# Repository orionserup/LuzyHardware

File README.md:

# LuzyHardware
A Hardware device that glows different colors depending on settings

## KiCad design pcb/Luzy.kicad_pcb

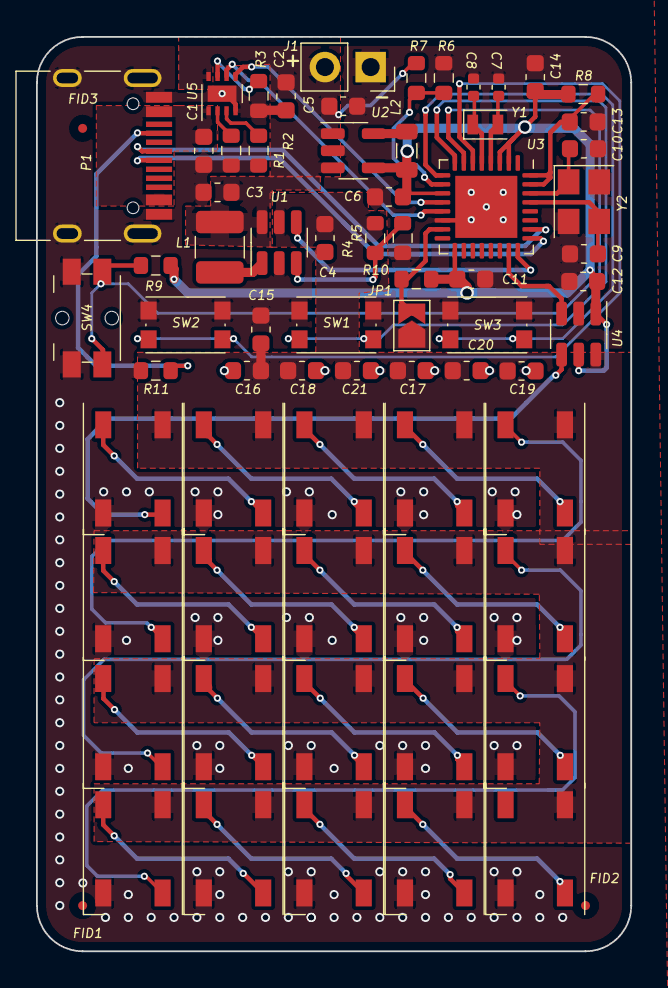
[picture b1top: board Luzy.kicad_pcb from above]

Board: 2 copper layers, 33.0 x 50.8 mm, 71 parts (0 on the bottom side), 49 nets.

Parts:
C1, C2, C3, C4, C5, C6, C11, C12, C13, C14, C15, C16, C17, C18, C19, C20, C21: 4.7uF; C_0603_1608Metric
C7, C8: 15-21pF; C_0402_1005Metric
C9, C10: 14-20pF; C_0603_1608Metric
D1, D2, D3, D4, D5, D6, D7, D8, D9, D10, D11, D12, D13, D14, D15, D16, D17, D18, D19, D20: WS2812B; LED_WS2812B_PLCC4_5.0x5.0mm_P3.2mm
FID1, FID2, FID3: Fiducial; Fiducial_0.5mm_Mask1.5mm
J1: Battery Connector; PinSocket_1x02_P2.54mm_Vertical
JP1: Jumper_2_Open; SolderJumper-2_P1.3mm_Open_TrianglePad1.0x1.5mm
L1: 4.7uH; L_1210_3225Metric
L2: 2.2uH; L_0805_2012Metric
P1: USB4105; USB_C_Receptacle_HRO_TYPE-C-31-M-12
R1: 500; R_0603_1608Metric
R2: 10k; R_0603_1608Metric
R3: 27k; R_0603_1608Metric
R4, R5: R_US; R_0603_1608Metric
R6, R7: 100k; R_0603_1608Metric
R8, R9, R10: 16.9k; R_0603_1608Metric
R11: 5.1k; R_0603_1608Metric
SW1, SW2, SW3: KMR211; SW_Push_1P1T_NO_CK_KMR2
SW4: EVQ-PUM02K; Panasonic_EVQPUM_EVQPUD
U1: TLV61070A; SOT-23-6
U2: LM3671; TSOT-23-5
U3: ESP32-C3; QFN-32-1EP_5x5mm_P0.5mm_EP3.45x3.45mm
U4: SN74LVC1T45DBV; SOT-23-6
U5: BQ25170JDSGR; WSON-8-1EP_2x2mm_P0.5mm_EP0.9x1.6mm
Y1: 32.768kHz 12.5pF; Crystal_SMD_2012-2Pin_2.0x1.2mm
Y2: 40MHz 12pF; Crystal_SMD_3225-4Pin_3.2x2.5mm

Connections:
/BOOST_EN: U1.4 (EN), U3.24 (SPIQ/GPIO17)
/CHRG_PG: U3.13 (MTDO/GPIO7), U5.6 (PG)
/CHRG_STAT: U3.12 (MTCK/GPIO6), U5.5 (STAT)
/Controller/BOOT: JP1.2 (B), R10.1, U3.15 (GPIO9/BOOT)
/Controller/VBATTSENSE: R6.2, R7.1, U3.10 (MTDI/GPIO5/ADC2_CH0)
/Controller/VDDA: C13.1, R8.2, U3.31 (VDDA), U3.32 (VDDA)
/Controller/WS2812_DATA: U3.23 (SPID/GPIO16), U4.3 (A)
/Controller/~RESET: R9.1, SW4.2 (B), U3.7 (CHIP_EN)
/D+: P1.A6 (D+), U3.26 (GPIO19/USB_D+)
/D-: P1.A7 (D-), U3.25 (GPIO18/USB_D-)
/DATA: D1.4 (DIN), U4.4 (B)
/GND: C1.2, C2.1, C3.2, C4.2, C5.2, C6.2, C7.1, C8.1, C9.1, C10.1, C11.1, C12.1, C13.2, C14.1, C15.1, C16.2, C17.2, C18.2, C19.2, C20.2, C21.2, D1.3 (VSS), D2.3 (VSS), D3.3 (VSS), D4.3 (VSS), D5.3 (VSS), D6.3 (VSS), D7.3 (VSS), D8.3 (VSS), D9.3 (VSS), D10.3 (VSS), D11.3 (VSS), D12.3 (VSS), D13.3 (VSS), D14.3 (VSS), D15.3 (VSS), D16.3 (VSS), D17.3 (VSS), D18.3 (VSS), D19.3 (VSS), D20.3 (VSS), J1.1, JP1.1 (A), P1.A1 (GND), P1.A12 (GND), P1.B1 (GND), P1.B12 (GND), P1.S1 (SHIELD), R1.2, R2.2, R3.1, R5.2, R7.2, R11.2, SW1.1 (A), SW2.1 (A), SW3.1 (A), SW4.1 (A), U1.2 (GND), U2.2 (GND), U3.14 (GPIO8), U3.33 (GND), U4.2 (GND), U5.4 (GND), U5.9 (EPAD), Y2.2, Y2.4
/LED Grid/LED Row1/DATA_OUT: D10.2 (DOUT), D11.4 (DIN)
/LED Grid/LED Row2/DATA_OUT: D15.2 (DOUT), D16.4 (DIN)
/LED Grid/LED Row/DATA_OUT: D5.2 (DOUT), D6.4 (DIN)
/LEFT: SW2.2 (B), U3.6 (GPIO2/ADC1_CH2)
/POWER: SW1.2 (B), U3.8 (GPIO3/ADC1_CH3)
/RIGHT: SW3.2 (B), U3.9 (MTMS/GPIO4/ADC1_CH4)
/V_{BATT}: C2.2, C3.1, C5.1, J1.2, L1.1, R6.1, U1.6 (VI), U2.1 (Vin), U2.3 (EN), U5.8 (OUT)
/V_{DD}: C6.1, C11.2, C12.2, C14.2, L2.2, R8.1, R9.2, R10.2, U2.4 (FB), U3.2 (VDD3P3), U3.3 (VDD3P3), U3.11 (VDD3P3_RTC), U3.17 (VDD3P3_CPU), U4.1 (VCCA), U4.5 (DIR)
/V_{LED}: C4.1, C15.2, C16.1, C17.1, C18.1, C19.1, C20.1, C21.1, D1.1 (VDD), D2.1 (VDD), D3.1 (VDD), D4.1 (VDD), D5.1 (VDD), D6.1 (VDD), D7.1 (VDD), D8.1 (VDD), D9.1 (VDD), D10.1 (VDD), D11.1 (VDD), D12.1 (VDD), D13.1 (VDD), D14.1 (VDD), D15.1 (VDD), D16.1 (VDD), D17.1 (VDD), D18.1 (VDD), D19.1 (VDD), D20.1 (VDD), R4.1, U1.5 (VOUT), U4.6 (VCCB)
/V_{USB}: C1.1, P1.A4 (VBUS), P1.A9 (VBUS), P1.B4 (VBUS), P1.B9 (VBUS), U5.1 (IN)
unnamed: C7.2, U3.4 (XTAL_32K_P/ADC1_CH0), Y1.2
unnamed: C8.2, U3.5 (XTAL_32K_N/ADC1_CH1), Y1.1
unnamed: C9.2, U3.29 (XTAL_N), Y2.3
unnamed: C10.2, U3.30 (XTAL_P), Y2.1
unnamed: D1.2 (DOUT), D2.4 (DIN)
unnamed: D2.2 (DOUT), D3.4 (DIN)
unnamed: D3.2 (DOUT), D4.4 (DIN)
unnamed: D4.2 (DOUT), D5.4 (DIN)
unnamed: D6.2 (DOUT), D7.4 (DIN)
unnamed: D7.2 (DOUT), D8.4 (DIN)
unnamed: D8.2 (DOUT), D9.4 (DIN)
unnamed: D9.2 (DOUT), D10.4 (DIN)
unnamed: D11.2 (DOUT), D12.4 (DIN)
unnamed: D12.2 (DOUT), D13.4 (DIN)
unnamed: D13.2 (DOUT), D14.4 (DIN)
unnamed: D14.2 (DOUT), D15.4 (DIN)
unnamed: D16.2 (DOUT), D17.4 (DIN)
unnamed: D17.2 (DOUT), D18.4 (DIN)
unnamed: D18.2 (DOUT), D19.4 (DIN)
unnamed: D19.2 (DOUT), D20.4 (DIN)
unnamed: L1.2, U1.1 (SW)
unnamed: L2.1, U2.5 (SW)
unnamed: P1.A5 (CC), R11.1
unnamed: R1.1, U5.2 (ISET)
unnamed: R2.1, U5.3 (TS)
unnamed: R3.2, U5.7 (VSET)
unnamed: R4.2, R5.1, U1.3 (FB)

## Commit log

2023-02-01 First Revision
2023-02-02 First Viable version
2023-02-02 Finished First Version
2023-02-03 Help
